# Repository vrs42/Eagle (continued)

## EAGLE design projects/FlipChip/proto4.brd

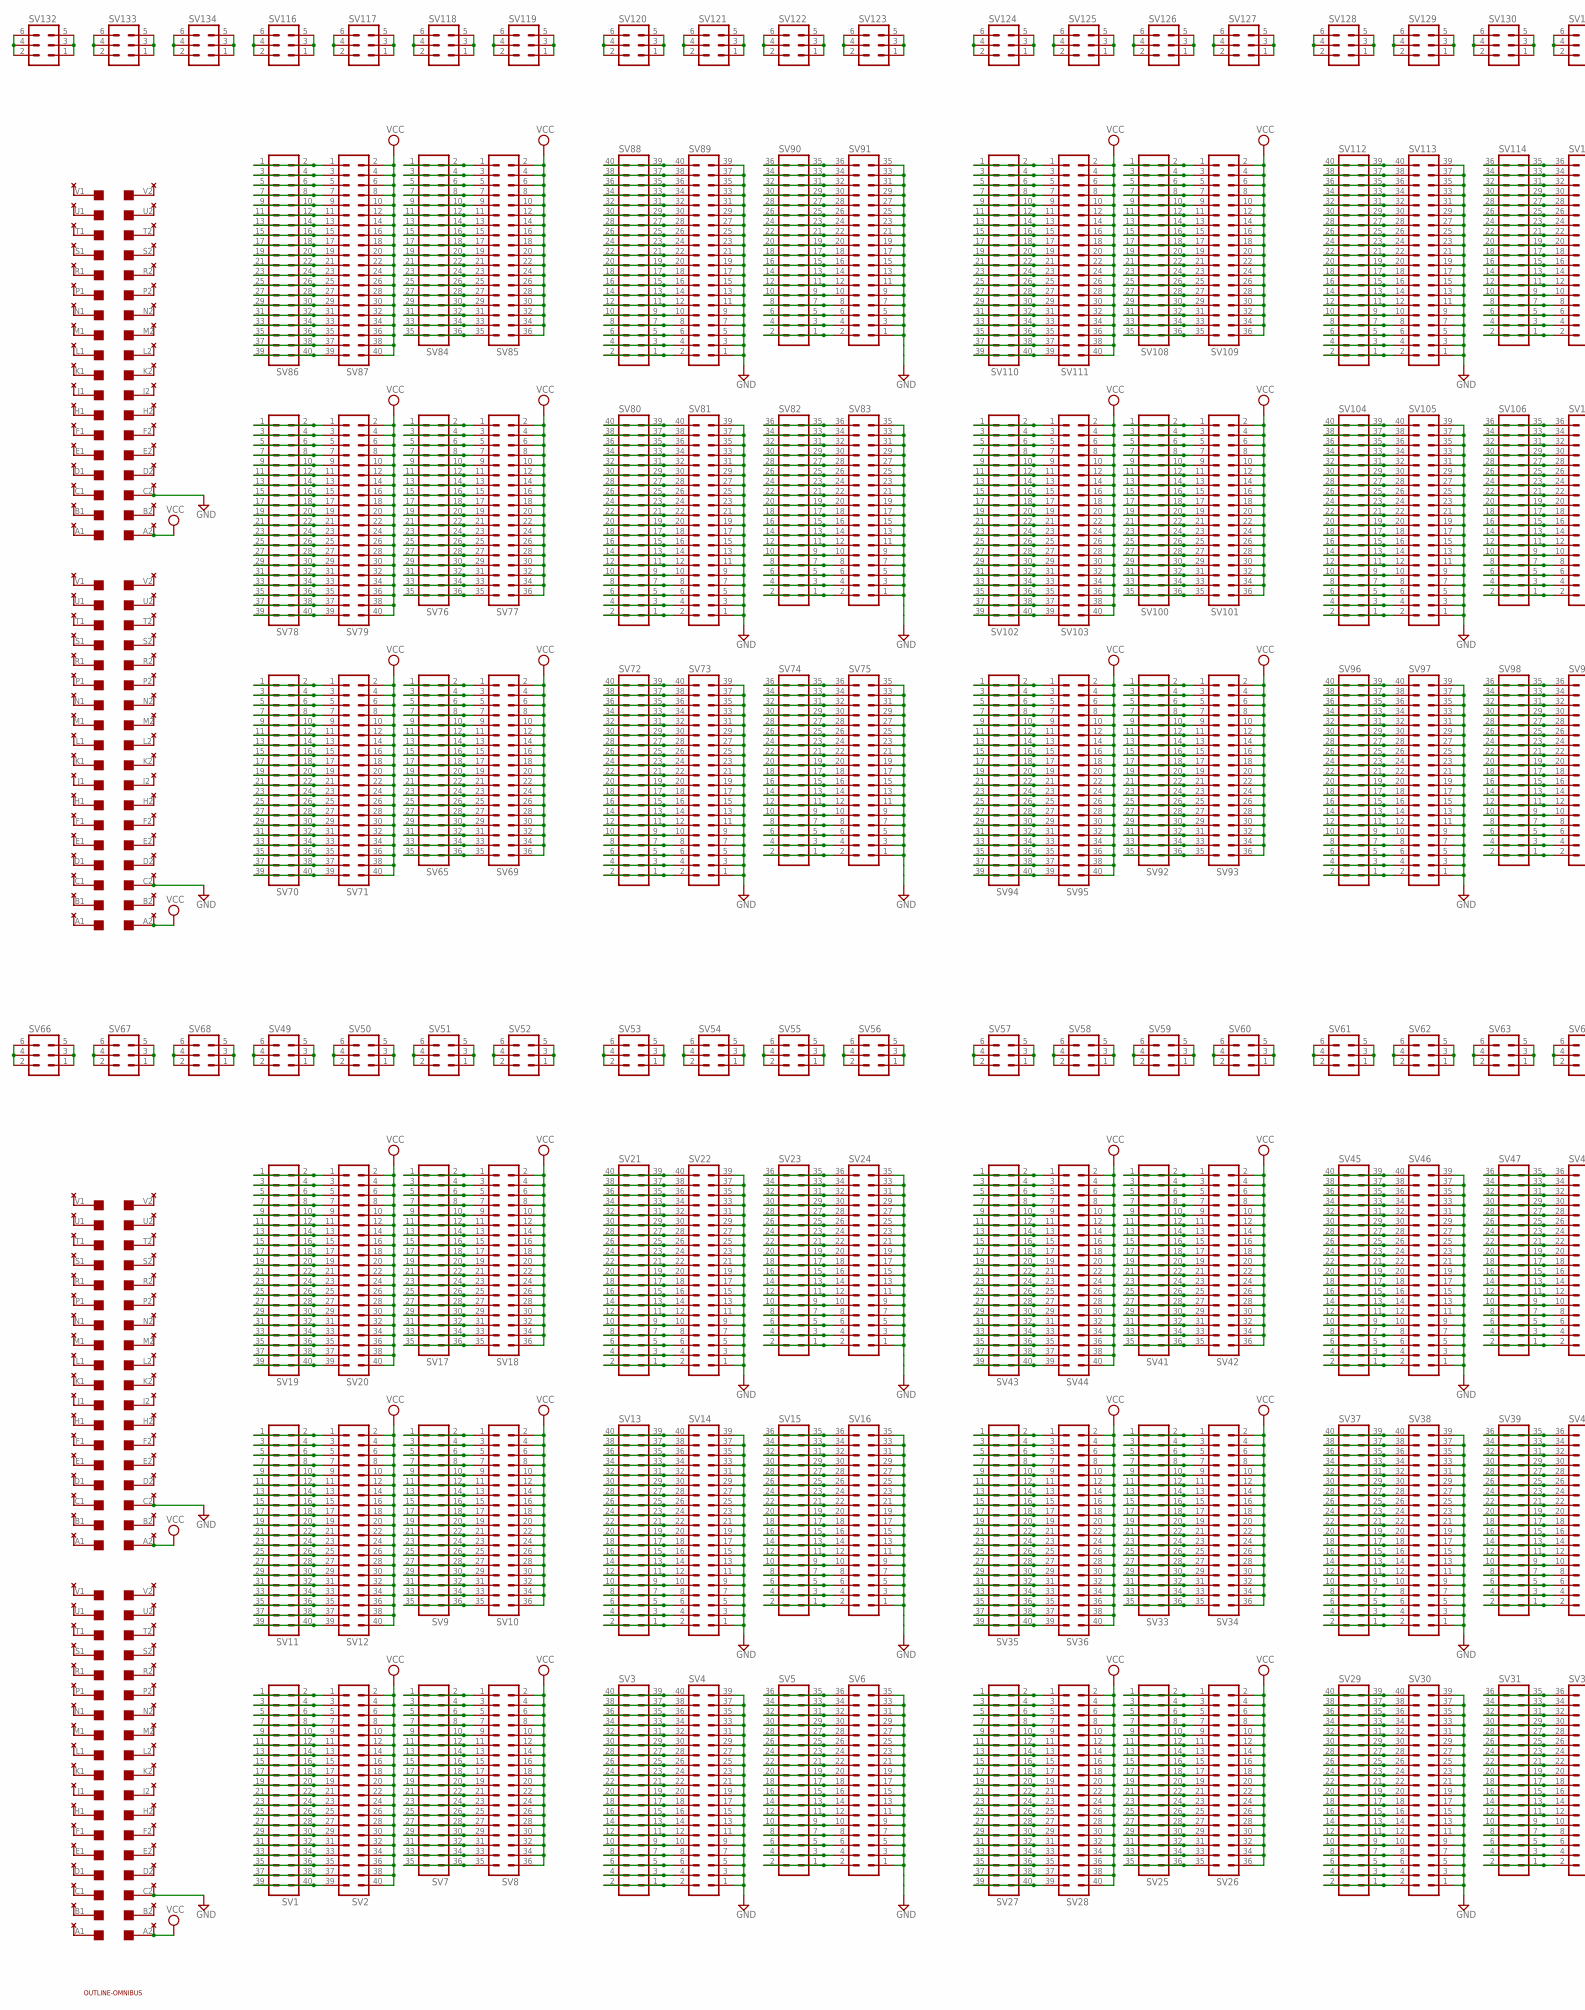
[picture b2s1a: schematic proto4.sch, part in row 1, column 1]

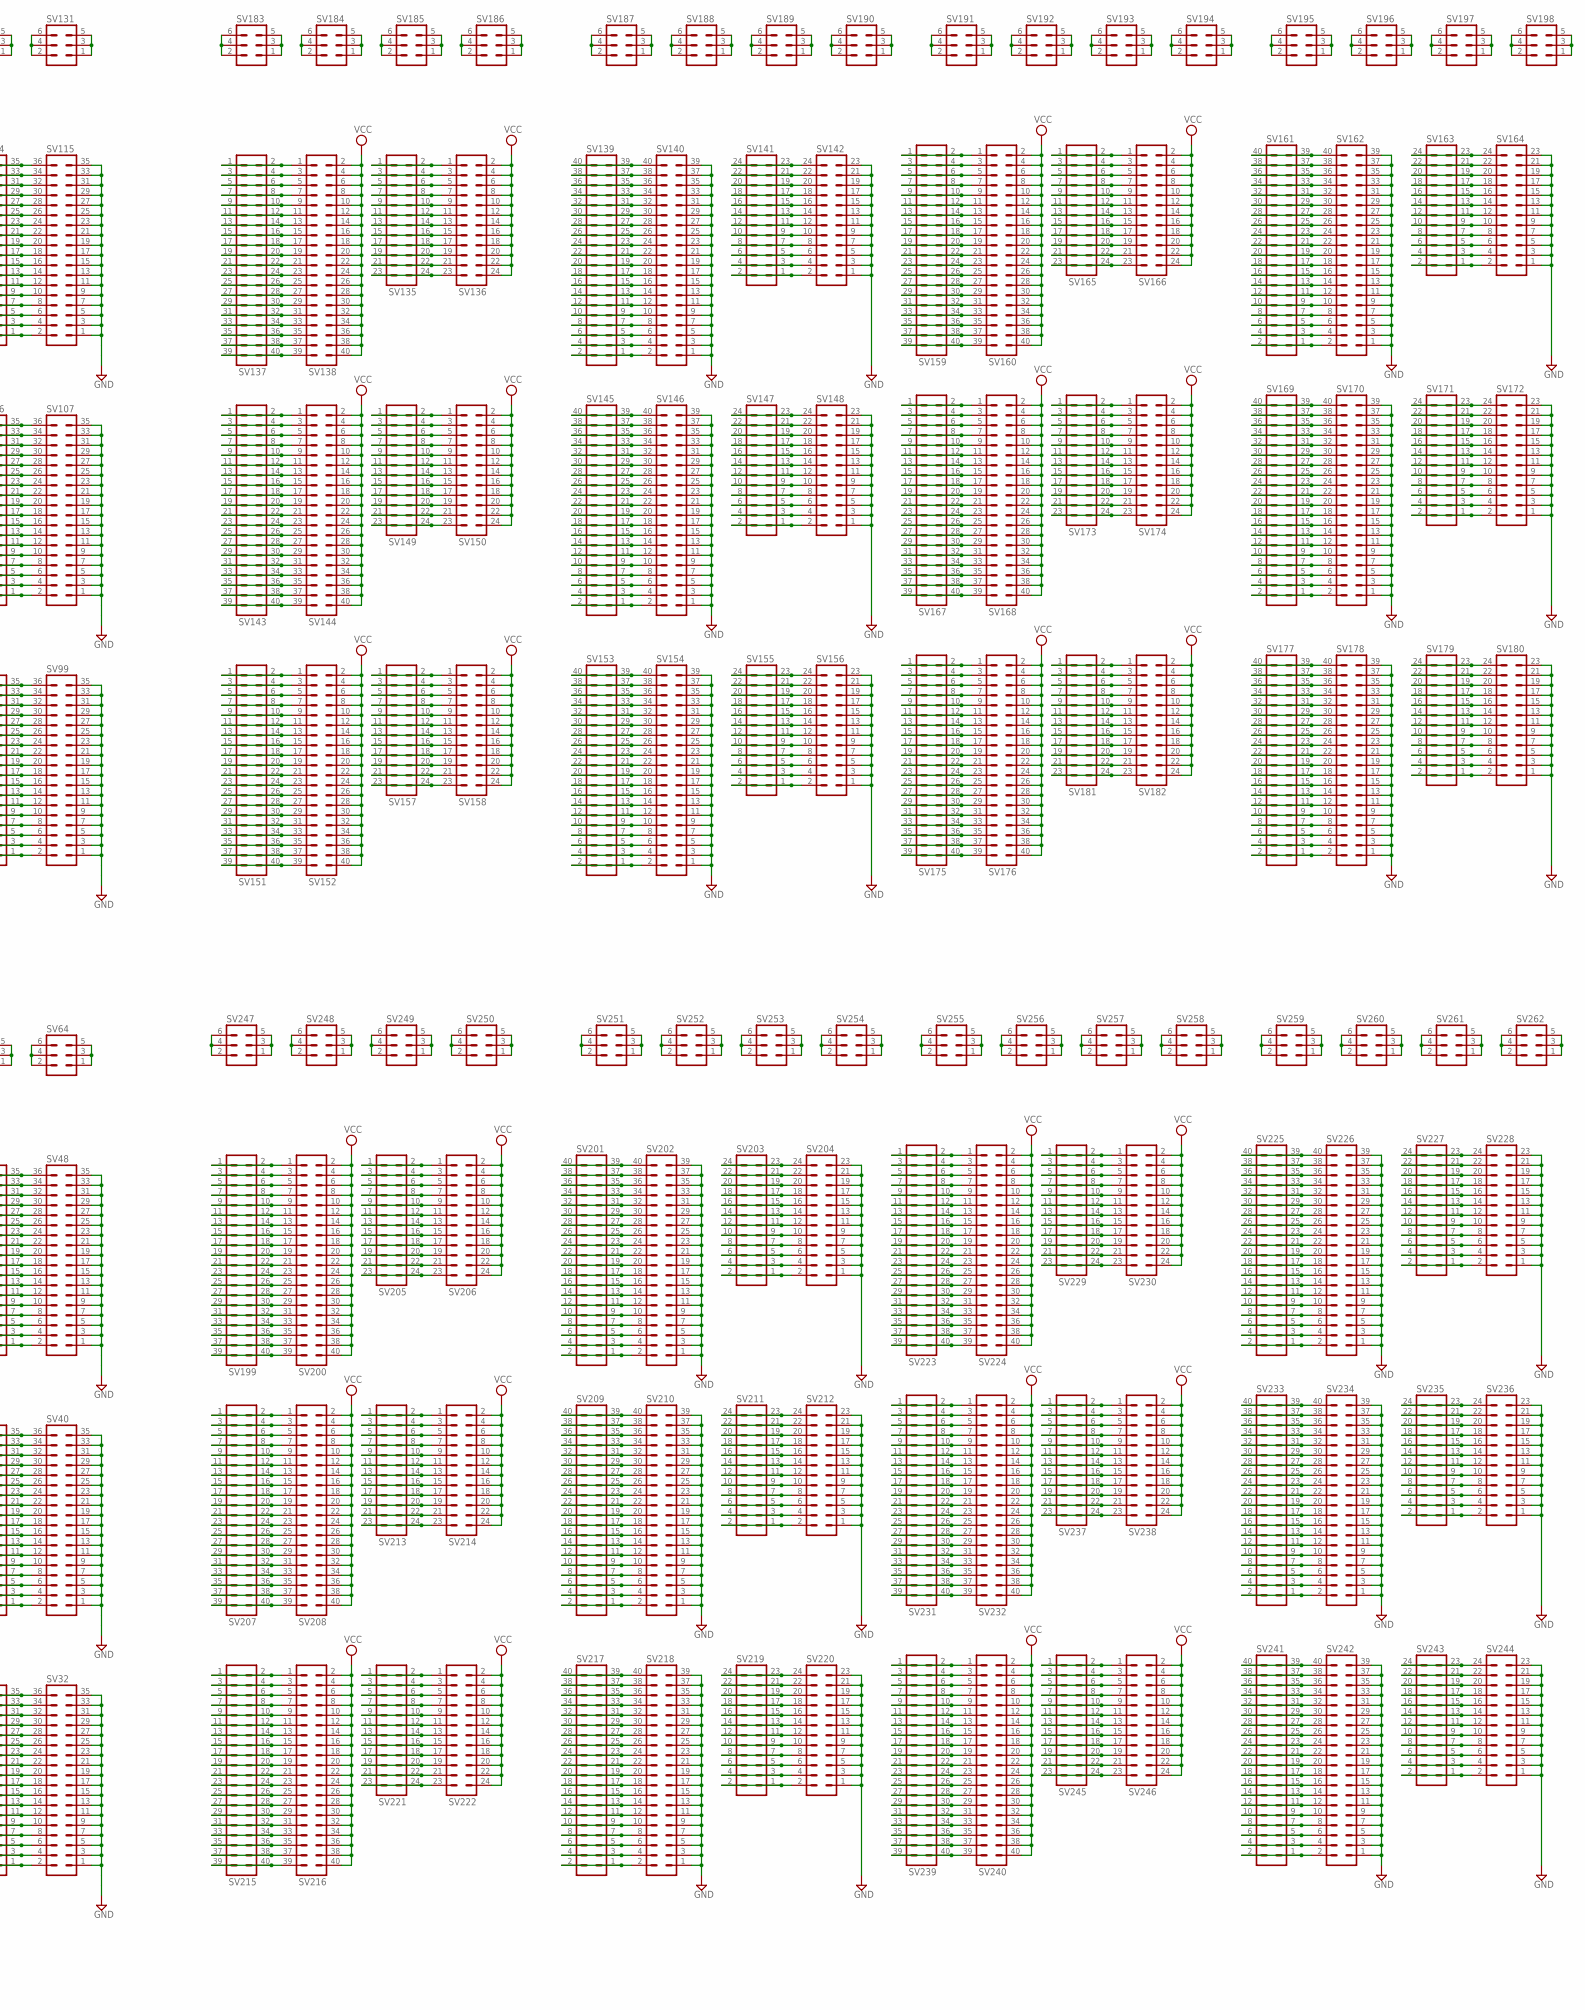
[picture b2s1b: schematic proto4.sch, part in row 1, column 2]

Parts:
A, A1: EDGE-2CONNECTOR; EDGE-CON2
B, B1: EDGE-2CONNECTOR; EDGE-CON2
SV1, SV2, SV3, SV4, SV11, SV12, SV13, SV14, SV19, SV20, SV21, SV22, SV27, SV28, SV29, SV30, SV35, SV36, SV37, SV38, SV43, SV44, SV45, SV46, SV70, SV71, SV72, SV73, SV78, SV79, SV80, SV81, SV86, SV87, SV88, SV89, SV94, SV95, SV96, SV97, SV102, SV103, SV104, SV105, SV110, SV111, SV112, SV113, SV137, SV138, SV139, SV140, SV143, SV144, SV145, SV146, SV151, SV152, SV153, SV154, SV159, SV160, SV161, SV162, SV167, SV168, SV169, SV170, SV175, SV176, SV177, SV178, SV199, SV200, SV201, SV202, SV207, SV208, SV209, SV210, SV215, SV216, SV217, SV218, SV223, SV224, SV225, SV226, SV231, SV232, SV233, SV234, SV239, SV240, SV241, SV242: MA20-2
SV5, SV6, SV7, SV8, SV9, SV10, SV15, SV16, SV17, SV18, SV23, SV24, SV25, SV26, SV31, SV32, SV33, SV34, SV39, SV40, SV41, SV42, SV47, SV48, SV65, SV69, SV74, SV75, SV76, SV77, SV82, SV83, SV84, SV85, SV90, SV91, SV92, SV93, SV98, SV99, SV100, SV101, SV106, SV107, SV108, SV109, SV114, SV115: MA18-2
SV49, SV50, SV51, SV52, SV53, SV54, SV55, SV56, SV57, SV58, SV59, SV60, SV61, SV62, SV63, SV64, SV66, SV67, SV68, SV116, SV117, SV118, SV119, SV120, SV121, SV122, SV123, SV124, SV125, SV126, SV127, SV128, SV129, SV130, SV131, SV132, SV133, SV134, SV183, SV184, SV185, SV186, SV187, SV188, SV189, SV190, SV191, SV192, SV193, SV194, SV195, SV196, SV197, SV198, SV247, SV248, SV249, SV250, SV251, SV252, SV253, SV254, SV255, SV256, SV257, SV258, SV259, SV260, SV261, SV262: MA03-2
SV135, SV136, SV141, SV142, SV147, SV148, SV149, SV150, SV155, SV156, SV157, SV158, SV163, SV164, SV165, SV166, SV171, SV172, SV173, SV174, SV179, SV180, SV181, SV182, SV203, SV204, SV205, SV206, SV211, SV212, SV213, SV214, SV219, SV220, SV221, SV222, SV227, SV228, SV229, SV230, SV235, SV236, SV237, SV238, SV243, SV244, SV245, SV246: MA12-2
U$1, U$3, U$5, U$6: THRU-HOLE2A; THRU-HOLEA
U$7: OUTLINE-OMNIBUS; OMNIBUS

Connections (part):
GND: A.C2, A1.C2, B.C2, B1.C2, SV4.1, SV4.3, SV4.5, SV4.7, SV4.9, SV4.11, SV4.13, SV4.15, SV4.17, SV4.19, SV4.21, SV4.23, SV4.25, SV4.27, SV4.29, SV4.31, SV4.33, SV4.35, SV4.37, SV4.39, SV6.1, SV6.3, SV6.5, SV6.7, SV6.9, SV6.11, SV6.13, SV6.15, SV6.17, SV6.19, SV6.21, SV6.23, SV6.25, SV6.27, SV6.29, SV6.31, SV6.33, SV6.35, SV14.1, SV14.3, SV14.5, SV14.7, SV14.9, SV14.11, SV14.13, SV14.15, SV14.17, SV14.19, SV14.21, SV14.23, SV14.25, SV14.27, SV14.29, SV14.31, SV14.33, SV14.35, SV14.37, SV14.39, SV16.1, SV16.3, SV16.5, SV16.7, SV16.9, SV16.11, SV16.13, SV16.15, SV16.17, SV16.19, SV16.21, SV16.23, SV16.25, SV16.27, SV16.29, SV16.31, SV16.33, SV16.35, SV22.1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
unnamed: A.K2, U$3.K2
unnamed: A.J2, U$3.J2
unnamed: A.H2, U$3.H2
unnamed: A.L2, U$3.L2
unnamed: A.M2, U$3.M2
unnamed: A.N2, U$3.N2
unnamed: A.P2, U$3.P2
unnamed: A.F2, U$3.F2
unnamed: A.E2, U$3.E2
unnamed: A.D2, U$3.D2
unnamed: SV1.1, SV1.2, SV2.1
unnamed: A.R2, U$3.R2
unnamed: A.S2, U$3.S2
unnamed: A.B2, U$3.B2
unnamed: SV1.3, SV1.4, SV2.3
unnamed: A.T2, U$3.T2
unnamed: A.U2, U$3.U2
unnamed: A.V2, U$3.V2
unnamed: A.A1, U$3.A1
unnamed: A.V1, U$3.V1
unnamed: A.U1, U$3.U1
unnamed: A.T1, U$3.T1
unnamed: A.S1, U$3.S1
unnamed: A.R1, U$3.R1
unnamed: A.P1, U$3.P1
unnamed: A.N1, U$3.N1
unnamed: A.M1, U$3.M1
unnamed: A.L1, U$3.L1
unnamed: A.K1, U$3.K1
unnamed: A.J1, U$3.J1
unnamed: A.H1, U$3.H1
unnamed: A.F1, U$3.F1
unnamed: A.E1, U$3.E1
unnamed: A.D1, U$3.D1
unnamed: A.C1, U$3.C1
unnamed: A.B1, U$3.B1
unnamed: SV1.5, SV1.6, SV2.5
unnamed: SV7.1, SV7.2, SV8.1
unnamed: SV7.3, SV7.4, SV8.3
unnamed: SV7.5, SV7.6, SV8.5
unnamed: SV7.7, SV7.8, SV8.7
unnamed: SV7.9, SV7.10, SV8.9
unnamed: SV7.11, SV7.12, SV8.11
unnamed: SV7.13, SV7.14, SV8.13
unnamed: SV1.7, SV1.8, SV2.7
unnamed: SV1.9, SV1.10, SV2.9
unnamed: SV1.11, SV1.12, SV2.11
unnamed: SV1.13, SV1.14, SV2.13
unnamed: SV1.15, SV1.16, SV2.15
unnamed: SV1.17, SV1.18, SV2.17
unnamed: SV1.19, SV1.20, SV2.19
unnamed: SV1.21, SV1.22, SV2.21
unnamed: SV1.23, SV1.24, SV2.23
unnamed: SV1.25, SV1.26, SV2.25
unnamed: SV1.27, SV1.28, SV2.27
unnamed: SV1.29, SV1.30, SV2.29
unnamed: SV1.31, SV1.32, SV2.31
unnamed: SV1.33, SV1.34, SV2.33
unnamed: SV1.35, SV1.36, SV2.35
unnamed: SV1.37, SV1.38, SV2.37
unnamed: SV1.39, SV1.40, SV2.39
unnamed: SV7.15, SV7.16, SV8.15
unnamed: SV7.17, SV7.18, SV8.17
unnamed: SV7.19, SV7.20, SV8.19
unnamed: SV7.21, SV7.22, SV8.21
unnamed: SV7.23, SV7.24, SV8.23
unnamed: SV7.25, SV7.26, SV8.25
unnamed: SV7.27, SV7.28, SV8.27
unnamed: SV7.29, SV7.30, SV8.29
unnamed: SV7.31, SV7.32, SV8.31
unnamed: SV7.33, SV7.34, SV8.33
unnamed: SV7.35, SV7.36, SV8.35
unnamed: SV3.39, SV3.40, SV4.40
unnamed: SV3.37, SV3.38, SV4.38
unnamed: SV3.35, SV3.36, SV4.36
unnamed: SV3.33, SV3.34, SV4.34
unnamed: SV3.31, SV3.32, SV4.32
unnamed: SV3.29, SV3.30, SV4.30
unnamed: SV3.27, SV3.28, SV4.28
unnamed: SV3.25, SV3.26, SV4.26
unnamed: SV3.23, SV3.24, SV4.24
unnamed: SV3.21, SV3.22, SV4.22
unnamed: SV3.19, SV3.20, SV4.20
unnamed: SV3.17, SV3.18, SV4.18
unnamed: SV3.15, SV3.16, SV4.16
unnamed: SV3.13, SV3.14, SV4.14
unnamed: SV3.11, SV3.12, SV4.12
unnamed: SV3.9, SV3.10, SV4.10
unnamed: SV3.7, SV3.8, SV4.8
unnamed: SV3.5, SV3.6, SV4.6
unnamed: SV3.3, SV3.4, SV4.4
unnamed: SV3.1, SV3.2, SV4.2
unnamed: SV11.1, SV11.2, SV12.1
unnamed: SV5.35, SV5.36, SV6.36
unnamed: SV5.33, SV5.34, SV6.34
unnamed: SV5.31, SV5.32, SV6.32
unnamed: SV5.29, SV5.30, SV6.30
unnamed: SV5.27, SV5.28, SV6.28
unnamed: SV5.25, SV5.26, SV6.26
unnamed: SV5.23, SV5.24, SV6.24
unnamed: SV5.21, SV5.22, SV6.22
unnamed: SV5.19, SV5.20, SV6.20
unnamed: SV5.17, SV5.18, SV6.18
unnamed: SV5.15, SV5.16, SV6.16
unnamed: SV5.13, SV5.14, SV6.14
unnamed: SV5.11, SV5.12, SV6.12
unnamed: SV5.9, SV5.10, SV6.10
unnamed: SV5.7, SV5.8, SV6.8
unnamed: SV5.5, SV5.6, SV6.6
unnamed: SV5.3, SV5.4, SV6.4
unnamed: SV5.1, SV5.2, SV6.2
unnamed: SV11.3, SV11.4, SV12.3
unnamed: SV11.5, SV11.6, SV12.5
unnamed: SV11.7, SV11.8, SV12.7
unnamed: SV11.9, SV11.10, SV12.9
unnamed: SV11.11, SV11.12, SV12.11
unnamed: SV11.13, SV11.14, SV12.13
unnamed: SV11.15, SV11.16, SV12.15
unnamed: SV11.17, SV11.18, SV12.17
unnamed: SV11.19, SV11.20, SV12.19
unnamed: SV11.21, SV11.22, SV12.21
unnamed: SV11.23, SV11.24, SV12.23
unnamed: SV11.25, SV11.26, SV12.25
unnamed: SV11.27, SV11.28, SV12.27
unnamed: SV11.29, SV11.30, SV12.29
unnamed: SV11.31, SV11.32, SV12.31
unnamed: SV11.33, SV11.34, SV12.33
unnamed: SV11.35, SV11.36, SV12.35
unnamed: SV11.37, SV11.38, SV12.37
unnamed: SV11.39, SV11.40, SV12.39
unnamed: SV9.1, SV9.2, SV10.1
unnamed: SV9.3, SV9.4, SV10.3
unnamed: SV9.5, SV9.6, SV10.5
unnamed: SV9.7, SV9.8, SV10.7
unnamed: SV9.9, SV9.10, SV10.9
unnamed: SV9.11, SV9.12, SV10.11
unnamed: SV9.13, SV9.14, SV10.13
unnamed: SV9.15, SV9.16, SV10.15
unnamed: SV9.17, SV9.18, SV10.17
unnamed: SV9.19, SV9.20, SV10.19
unnamed: SV9.21, SV9.22, SV10.21
unnamed: SV9.23, SV9.24, SV10.23
unnamed: SV9.25, SV9.26, SV10.25
unnamed: SV9.27, SV9.28, SV10.27
unnamed: SV9.29, SV9.30, SV10.29
unnamed: SV9.31, SV9.32, SV10.31
unnamed: SV9.33, SV9.34, SV10.33
unnamed: SV9.35, SV9.36, SV10.35
unnamed: SV13.39, SV13.40, SV14.40
unnamed: SV13.37, SV13.38, SV14.38
unnamed: SV13.35, SV13.36, SV14.36
unnamed: SV13.33, SV13.34, SV14.34
unnamed: SV13.31, SV13.32, SV14.32
unnamed: SV13.29, SV13.30, SV14.30
unnamed: SV13.27, SV13.28, SV14.28
unnamed: SV13.25, SV13.26, SV14.26
unnamed: SV13.23, SV13.24, SV14.24
unnamed: SV13.21, SV13.22, SV14.22
unnamed: SV13.19, SV13.20, SV14.20
unnamed: SV13.17, SV13.18, SV14.18
unnamed: SV13.15, SV13.16, SV14.16
unnamed: SV13.13, SV13.14, SV14.14
unnamed: SV13.11, SV13.12, SV14.12
unnamed: SV13.9, SV13.10, SV14.10
unnamed: SV13.7, SV13.8, SV14.8
unnamed: SV13.5, SV13.6, SV14.6
unnamed: SV13.3, SV13.4, SV14.4
unnamed: SV13.1, SV13.2, SV14.2
unnamed: SV15.35, SV15.36, SV16.36
unnamed: SV15.33, SV15.34, SV16.34
unnamed: SV15.31, SV15.32, SV16.32
unnamed: SV15.29, SV15.30, SV16.30
unnamed: SV15.27, SV15.28, SV16.28
unnamed: SV15.25, SV15.26, SV16.26
unnamed: SV15.23, SV15.24, SV16.24
unnamed: SV15.21, SV15.22, SV16.22
unnamed: SV15.19, SV15.20, SV16.20
unnamed: SV15.17, SV15.18, SV16.18
unnamed: SV15.15, SV15.16, SV16.16
unnamed: SV15.13, SV15.14, SV16.14
unnamed: SV15.11, SV15.12, SV16.12
unnamed: SV15.9, SV15.10, SV16.10
unnamed: SV15.7, SV15.8, SV16.8
unnamed: SV15.5, SV15.6, SV16.6
unnamed: SV15.3, SV15.4, SV16.4
unnamed: SV15.1, SV15.2, SV16.2
unnamed: SV19.1, SV19.2, SV20.1
unnamed: SV19.3, SV19.4, SV20.3
unnamed: SV19.5, SV19.6, SV20.5
unnamed: SV19.7, SV19.8, SV20.7
unnamed: SV19.9, SV19.10, SV20.9
unnamed: SV19.11, SV19.12, SV20.11
unnamed: SV19.13, SV19.14, SV20.13
unnamed: SV19.15, SV19.16, SV20.15
unnamed: SV19.17, SV19.18, SV20.17
unnamed: SV19.19, SV19.20, SV20.19
unnamed: SV19.21, SV19.22, SV20.21
unnamed: SV19.23, SV19.24, SV20.23
unnamed: SV19.25, SV19.26, SV20.25
unnamed: SV19.27, SV19.28, SV20.27
unnamed: SV19.29, SV19.30, SV20.29
unnamed: SV19.31, SV19.32, SV20.31
unnamed: SV19.33, SV19.34, SV20.33
unnamed: SV19.35, SV19.36, SV20.35
unnamed: SV19.37, SV19.38, SV20.37
unnamed: SV19.39, SV19.40, SV20.39
unnamed: SV17.1, SV17.2, SV18.1
unnamed: SV17.3, SV17.4, SV18.3
unnamed: SV17.5, SV17.6, SV18.5
unnamed: SV17.7, SV17.8, SV18.7
unnamed: SV17.9, SV17.10, SV18.9
unnamed: SV17.11, SV17.12, SV18.11
unnamed: SV17.13, SV17.14, SV18.13
unnamed: SV17.15, SV17.16, SV18.15
unnamed: SV17.17, SV17.18, SV18.17
unnamed: SV17.19, SV17.20, SV18.19
unnamed: SV17.21, SV17.22, SV18.21
unnamed: SV17.23, SV17.24, SV18.23
unnamed: SV17.25, SV17.26, SV18.25
unnamed: SV17.27, SV17.28, SV18.27
unnamed: SV17.29, SV17.30, SV18.29
unnamed: SV17.31, SV17.32, SV18.31
unnamed: SV17.33, SV17.34, SV18.33
unnamed: SV17.35, SV17.36, SV18.35
unnamed: SV21.39, SV21.40, SV22.40
unnamed: SV21.37, SV21.38, SV22.38
unnamed: SV21.35, SV21.36, SV22.36
unnamed: SV21.33, SV21.34, SV22.34
unnamed: SV21.31, SV21.32, SV22.32
unnamed: SV21.29, SV21.30, SV22.30
unnamed: SV21.27, SV21.28, SV22.28
unnamed: SV21.25, SV21.26, SV22.26
unnamed: SV21.23, SV21.24, SV22.24
unnamed: SV21.21, SV21.22, SV22.22
unnamed: SV21.19, SV21.20, SV22.20
unnamed: SV21.17, SV21.18, SV22.18
unnamed: SV21.15, SV21.16, SV22.16
unnamed: SV21.13, SV21.14, SV22.14
unnamed: SV21.11, SV21.12, SV22.12
unnamed: SV21.9, SV21.10, SV22.10
unnamed: SV21.7, SV21.8, SV22.8
unnamed: SV21.5, SV21.6, SV22.6
unnamed: SV21.3, SV21.4, SV22.4
unnamed: SV21.1, SV21.2, SV22.2
unnamed: SV23.35, SV23.36, SV24.36
unnamed: SV23.33, SV23.34, SV24.34
unnamed: SV23.31, SV23.32, SV24.32
unnamed: SV23.29, SV23.30, SV24.30
unnamed: SV23.27, SV23.28, SV24.28
unnamed: SV23.25, SV23.26, SV24.26
unnamed: SV23.23, SV23.24, SV24.24
unnamed: SV23.21, SV23.22, SV24.22
unnamed: SV23.19, SV23.20, SV24.20
unnamed: SV23.17, SV23.18, SV24.18
unnamed: SV23.15, SV23.16, SV24.16
unnamed: SV23.13, SV23.14, SV24.14
unnamed: SV23.11, SV23.12, SV24.12
unnamed: SV23.9, SV23.10, SV24.10
unnamed: SV23.7, SV23.8, SV24.8
unnamed: SV23.5, SV23.6, SV24.6
unnamed: SV23.3, SV23.4, SV24.4
unnamed: SV23.1, SV23.2, SV24.2
unnamed: B.K2, U$5.K2
unnamed: B.J2, U$5.J2
unnamed: B.H2, U$5.H2
unnamed: B.L2, U$5.L2
unnamed: B.M2, U$5.M2
unnamed: B.N2, U$5.N2
unnamed: B.P2, U$5.P2
unnamed: B.F2, U$5.F2
unnamed: B.E2, U$5.E2
unnamed: B.D2, U$5.D2
unnamed: B.R2, U$5.R2
unnamed: B.S2, U$5.S2
unnamed: B.B2, U$5.B2
unnamed: B.T2, U$5.T2
unnamed: B.U2, U$5.U2
unnamed: B.V2, U$5.V2
unnamed: B.A1, U$5.A1
unnamed: B.V1, U$5.V1
unnamed: B.U1, U$5.U1
unnamed: B.T1, U$5.T1
unnamed: B.S1, U$5.S1
unnamed: B.R1, U$5.R1
unnamed: B.P1, U$5.P1
unnamed: B.N1, U$5.N1
unnamed: B.M1, U$5.M1
unnamed: B.L1, U$5.L1
unnamed: B.K1, U$5.K1
unnamed: B.J1, U$5.J1
unnamed: B.H1, U$5.H1
unnamed: B.F1, U$5.F1
unnamed: B.E1, U$5.E1
unnamed: B.D1, U$5.D1
unnamed: B.C1, U$5.C1
unnamed: B.B1, U$5.B1
unnamed: SV27.1, SV27.2, SV28.1
unnamed: SV27.3, SV27.4, SV28.3
unnamed: SV27.5, SV27.6, SV28.5
unnamed: SV27.7, SV27.8, SV28.7
unnamed: SV27.9, SV27.10, SV28.9
unnamed: SV27.11, SV27.12, SV28.11
unnamed: SV27.13, SV27.14, SV28.13
unnamed: SV27.15, SV27.16, SV28.15
unnamed: SV27.17, SV27.18, SV28.17
unnamed: SV27.19, SV27.20, SV28.19
unnamed: SV27.21, SV27.22, SV28.21
unnamed: SV27.23, SV27.24, SV28.23
unnamed: SV27.25, SV27.26, SV28.25
unnamed: SV27.27, SV27.28, SV28.27
unnamed: SV27.29, SV27.30, SV28.29
unnamed: SV27.31, SV27.32, SV28.31
unnamed: SV27.33, SV27.34, SV28.33
unnamed: SV27.35, SV27.36, SV28.35
unnamed: SV27.37, SV27.38, SV28.37
unnamed: SV27.39, SV27.40, SV28.39
unnamed: SV25.1, SV25.2, SV26.1
unnamed: SV25.3, SV25.4, SV26.3
unnamed: SV25.5, SV25.6, SV26.5
unnamed: SV25.7, SV25.8, SV26.7
unnamed: SV25.9, SV25.10, SV26.9
unnamed: SV25.11, SV25.12, SV26.11
unnamed: SV25.13, SV25.14, SV26.13
unnamed: SV25.15, SV25.16, SV26.15
unnamed: SV25.17, SV25.18, SV26.17
unnamed: SV25.19, SV25.20, SV26.19
unnamed: SV25.21, SV25.22, SV26.21
unnamed: SV25.23, SV25.24, SV26.23
unnamed: SV25.25, SV25.26, SV26.25
unnamed: SV25.27, SV25.28, SV26.27
unnamed: SV25.29, SV25.30, SV26.29
unnamed: SV25.31, SV25.32, SV26.31
unnamed: SV25.33, SV25.34, SV26.33
unnamed: SV25.35, SV25.36, SV26.35
unnamed: SV29.39, SV29.40, SV30.40
unnamed: SV29.37, SV29.38, SV30.38
unnamed: SV29.35, SV29.36, SV30.36
unnamed: SV29.33, SV29.34, SV30.34
unnamed: SV29.31, SV29.32, SV30.32
unnamed: SV29.29, SV29.30, SV30.30
unnamed: SV29.27, SV29.28, SV30.28
unnamed: SV29.25, SV29.26, SV30.26
unnamed: SV29.23, SV29.24, SV30.24
unnamed: SV29.21, SV29.22, SV30.22
unnamed: SV29.19, SV29.20, SV30.20
unnamed: SV29.17, SV29.18, SV30.18
unnamed: SV29.15, SV29.16, SV30.16
unnamed: SV29.13, SV29.14, SV30.14
unnamed: SV29.11, SV29.12, SV30.12
unnamed: SV29.9, SV29.10, SV30.10
unnamed: SV29.7, SV29.8, SV30.8
unnamed: SV29.5, SV29.6, SV30.6
unnamed: SV29.3, SV29.4, SV30.4
unnamed: SV29.1, SV29.2, SV30.2
unnamed: SV31.35, SV31.36, SV32.36
unnamed: SV31.33, SV31.34, SV32.34
unnamed: SV31.31, SV31.32, SV32.32
unnamed: SV31.29, SV31.30, SV32.30
unnamed: SV31.27, SV31.28, SV32.28
unnamed: SV31.25, SV31.26, SV32.26
unnamed: SV31.23, SV31.24, SV32.24
unnamed: SV31.21, SV31.22, SV32.22
unnamed: SV31.19, SV31.20, SV32.20
unnamed: SV31.17, SV31.18, SV32.18
unnamed: SV31.15, SV31.16, SV32.16
unnamed: SV31.13, SV31.14, SV32.14
unnamed: SV31.11, SV31.12, SV32.12
unnamed: SV31.9, SV31.10, SV32.10
unnamed: SV31.7, SV31.8, SV32.8
unnamed: SV31.5, SV31.6, SV32.6
unnamed: SV31.3, SV31.4, SV32.4
unnamed: SV31.1, SV31.2, SV32.2
unnamed: SV35.1, SV35.2, SV36.1
unnamed: SV35.3, SV35.4, SV36.3
unnamed: SV35.5, SV35.6, SV36.5
unnamed: SV35.7, SV35.8, SV36.7
unnamed: SV35.9, SV35.10, SV36.9
unnamed: SV35.11, SV35.12, SV36.11
unnamed: SV35.13, SV35.14, SV36.13
unnamed: SV35.15, SV35.16, SV36.15
unnamed: SV35.17, SV35.18, SV36.17
unnamed: SV35.19, SV35.20, SV36.19
unnamed: SV35.21, SV35.22, SV36.21
unnamed: SV35.23, SV35.24, SV36.23
unnamed: SV35.25, SV35.26, SV36.25
unnamed: SV35.27, SV35.28, SV36.27
unnamed: SV35.29, SV35.30, SV36.29
unnamed: SV35.31, SV35.32, SV36.31
unnamed: SV35.33, SV35.34, SV36.33
unnamed: SV35.35, SV35.36, SV36.35
unnamed: SV35.37, SV35.38, SV36.37
unnamed: SV35.39, SV35.40, SV36.39
unnamed: SV33.1, SV33.2, SV34.1
unnamed: SV33.3, SV33.4, SV34.3
unnamed: SV33.5, SV33.6, SV34.5
unnamed: SV33.7, SV33.8, SV34.7
unnamed: SV33.9, SV33.10, SV34.9
unnamed: SV33.11, SV33.12, SV34.11
unnamed: SV33.13, SV33.14, SV34.13
unnamed: SV33.15, SV33.16, SV34.15
unnamed: SV33.17, SV33.18, SV34.17
unnamed: SV33.19, SV33.20, SV34.19
unnamed: SV33.21, SV33.22, SV34.21
unnamed: SV33.23, SV33.24, SV34.23
unnamed: SV33.25, SV33.26, SV34.25
unnamed: SV33.27, SV33.28, SV34.27
unnamed: SV33.29, SV33.30, SV34.29
unnamed: SV33.31, SV33.32, SV34.31
unnamed: SV33.33, SV33.34, SV34.33
unnamed: SV33.35, SV33.36, SV34.35
unnamed: SV37.39, SV37.40, SV38.40
unnamed: SV37.37, SV37.38, SV38.38
unnamed: SV37.35, SV37.36, SV38.36
unnamed: SV37.33, SV37.34, SV38.34
unnamed: SV37.31, SV37.32, SV38.32
unnamed: SV37.29, SV37.30, SV38.30
unnamed: SV37.27, SV37.28, SV38.28
unnamed: SV37.25, SV37.26, SV38.26
unnamed: SV37.23, SV37.24, SV38.24
unnamed: SV37.21, SV37.22, SV38.22
unnamed: SV37.19, SV37.20, SV38.20
unnamed: SV37.17, SV37.18, SV38.18
unnamed: SV37.15, SV37.16, SV38.16
unnamed: SV37.13, SV37.14, SV38.14
unnamed: SV37.11, SV37.12, SV38.12
unnamed: SV37.9, SV37.10, SV38.10
unnamed: SV37.7, SV37.8, SV38.8
unnamed: SV37.5, SV37.6, SV38.6
unnamed: SV37.3, SV37.4, SV38.4
unnamed: SV37.1, SV37.2, SV38.2
unnamed: SV39.35, SV39.36, SV40.36
unnamed: SV39.33, SV39.34, SV40.34
unnamed: SV39.31, SV39.32, SV40.32
unnamed: SV39.29, SV39.30, SV40.30
unnamed: SV39.27, SV39.28, SV40.28
unnamed: SV39.25, SV39.26, SV40.26
unnamed: SV39.23, SV39.24, SV40.24
unnamed: SV39.21, SV39.22, SV40.22
unnamed: SV39.19, SV39.20, SV40.20
unnamed: SV39.17, SV39.18, SV40.18
unnamed: SV39.15, SV39.16, SV40.16
unnamed: SV39.13, SV39.14, SV40.14
unnamed: SV39.11, SV39.12, SV40.12
unnamed: SV39.9, SV39.10, SV40.10
unnamed: SV39.7, SV39.8, SV40.8
unnamed: SV39.5, SV39.6, SV40.6
unnamed: SV39.3, SV39.4, SV40.4
unnamed: SV39.1, SV39.2, SV40.2
unnamed: SV43.1, SV43.2, SV44.1
unnamed: SV43.3, SV43.4, SV44.3
unnamed: SV43.5, SV43.6, SV44.5
unnamed: SV43.7, SV43.8, SV44.7
unnamed: SV43.9, SV43.10, SV44.9
unnamed: SV43.11, SV43.12, SV44.11
unnamed: SV43.13, SV43.14, SV44.13
unnamed: SV43.15, SV43.16, SV44.15
unnamed: SV43.17, SV43.18, SV44.17
unnamed: SV43.19, SV43.20, SV44.19
unnamed: SV43.21, SV43.22, SV44.21
unnamed: SV43.23, SV43.24, SV44.23
unnamed: SV43.25, SV43.26, SV44.25
unnamed: SV43.27, SV43.28, SV44.27
unnamed: SV43.29, SV43.30, SV44.29
unnamed: SV43.31, SV43.32, SV44.31
unnamed: SV43.33, SV43.34, SV44.33
unnamed: SV43.35, SV43.36, SV44.35
unnamed: SV43.37, SV43.38, SV44.37
unnamed: SV43.39, SV43.40, SV44.39
unnamed: SV41.1, SV41.2, SV42.1
unnamed: SV41.3, SV41.4, SV42.3
unnamed: SV41.5, SV41.6, SV42.5
unnamed: SV41.7, SV41.8, SV42.7
unnamed: SV41.9, SV41.10, SV42.9
unnamed: SV41.11, SV41.12, SV42.11
unnamed: SV41.13, SV41.14, SV42.13
unnamed: SV41.15, SV41.16, SV42.15
unnamed: SV41.17, SV41.18, SV42.17
unnamed: SV41.19, SV41.20, SV42.19
unnamed: SV41.21, SV41.22, SV42.21
unnamed: SV41.23, SV41.24, SV42.23
unnamed: SV41.25, SV41.26, SV42.25
unnamed: SV41.27, SV41.28, SV42.27
unnamed: SV41.29, SV41.30, SV42.29
unnamed: SV41.31, SV41.32, SV42.31
unnamed: SV41.33, SV41.34, SV42.33
unnamed: SV41.35, SV41.36, SV42.35
unnamed: SV45.39, SV45.40, SV46.40
unnamed: SV45.37, SV45.38, SV46.38
unnamed: SV45.35, SV45.36, SV46.36
unnamed: SV45.33, SV45.34, SV46.34
unnamed: SV45.31, SV45.32, SV46.32
unnamed: SV45.29, SV45.30, SV46.30
unnamed: SV45.27, SV45.28, SV46.28
unnamed: SV45.25, SV45.26, SV46.26
unnamed: SV45.23, SV45.24, SV46.24
unnamed: SV45.21, SV45.22, SV46.22
unnamed: SV45.19, SV45.20, SV46.20
unnamed: SV45.17, SV45.18, SV46.18
unnamed: SV45.15, SV45.16, SV46.16
unnamed: SV45.13, SV45.14, SV46.14
unnamed: SV45.11, SV45.12, SV46.12
unnamed: SV45.9, SV45.10, SV46.10
unnamed: SV45.7, SV45.8, SV46.8
unnamed: SV45.5, SV45.6, SV46.6
unnamed: SV45.3, SV45.4, SV46.4
unnamed: SV45.1, SV45.2, SV46.2
unnamed: SV47.35, SV47.36, SV48.36
unnamed: SV47.33, SV47.34, SV48.34
unnamed: SV47.31, SV47.32, SV48.32
unnamed: SV47.29, SV47.30, SV48.30
unnamed: SV47.27, SV47.28, SV48.28
unnamed: SV47.25, SV47.26, SV48.26
unnamed: SV47.23, SV47.24, SV48.24
unnamed: SV47.21, SV47.22, SV48.22
unnamed: SV47.19, SV47.20, SV48.20
unnamed: SV47.17, SV47.18, SV48.18
unnamed: SV47.15, SV47.16, SV48.16
unnamed: SV47.13, SV47.14, SV48.14
unnamed: SV47.11, SV47.12, SV48.12
unnamed: SV47.9, SV47.10, SV48.10
unnamed: SV47.7, SV47.8, SV48.8
unnamed: SV47.5, SV47.6, SV48.6
unnamed: SV47.3, SV47.4, SV48.4
unnamed: SV47.1, SV47.2, SV48.2
unnamed: SV66.2, SV66.4, SV66.6
unnamed: SV66.1, SV66.3, SV66.5
unnamed: SV67.2, SV67.4, SV67.6
unnamed: SV67.1, SV67.3, SV67.5
unnamed: SV68.2, SV68.4, SV68.6
unnamed: SV68.1, SV68.3, SV68.5
unnamed: SV49.2, SV49.4, SV49.6
unnamed: SV49.1, SV49.3, SV49.5
unnamed: SV50.2, SV50.4, SV50.6
unnamed: SV50.1, SV50.3, SV50.5
unnamed: SV51.2, SV51.4, SV51.6
unnamed: SV51.1, SV51.3, SV51.5
unnamed: SV52.1, SV52.3, SV52.5
unnamed: SV52.2, SV52.4, SV52.6
unnamed: SV53.2, SV53.4, SV53.6
unnamed: SV53.1, SV53.3, SV53.5
unnamed: SV54.2, SV54.4, SV54.6
unnamed: SV54.1, SV54.3, SV54.5
unnamed: SV55.2, SV55.4, SV55.6
unnamed: SV55.1, SV55.3, SV55.5
unnamed: SV56.2, SV56.4, SV56.6
unnamed: SV56.1, SV56.3, SV56.5
unnamed: SV57.2, SV57.4, SV57.6
unnamed: SV57.1, SV57.3, SV57.5
unnamed: SV58.2, SV58.4, SV58.6
unnamed: SV58.1, SV58.3, SV58.5
unnamed: SV59.2, SV59.4, SV59.6
unnamed: SV59.1, SV59.3, SV59.5
unnamed: SV60.2, SV60.4, SV60.6
unnamed: SV60.1, SV60.3, SV60.5
unnamed: SV61.2, SV61.4, SV61.6
unnamed: SV61.1, SV61.3, SV61.5
unnamed: SV62.2, SV62.4, SV62.6
unnamed: SV62.1, SV62.3, SV62.5
unnamed: SV63.2, SV63.4, SV63.6
unnamed: SV63.1, SV63.3, SV63.5
unnamed: SV64.2, SV64.4, SV64.6
unnamed: SV64.1, SV64.3, SV64.5
unnamed: A1.K2, U$1.K2
unnamed: A1.J2, U$1.J2
unnamed: A1.H2, U$1.H2
unnamed: A1.L2, U$1.L2
unnamed: A1.M2, U$1.M2
unnamed: A1.N2, U$1.N2
unnamed: A1.P2, U$1.P2
unnamed: A1.F2, U$1.F2
unnamed: A1.E2, U$1.E2
unnamed: A1.D2, U$1.D2
unnamed: A1.R2, U$1.R2
unnamed: A1.S2, U$1.S2
unnamed: A1.B2, U$1.B2
unnamed: A1.T2, U$1.T2
unnamed: A1.U2, U$1.U2
unnamed: A1.V2, U$1.V2
unnamed: A1.A1, U$1.A1
unnamed: A1.V1, U$1.V1
unnamed: A1.U1, U$1.U1
unnamed: A1.T1, U$1.T1
unnamed: A1.S1, U$1.S1
unnamed: A1.R1, U$1.R1
unnamed: A1.P1, U$1.P1
unnamed: A1.N1, U$1.N1
unnamed: A1.M1, U$1.M1
unnamed: A1.L1, U$1.L1
unnamed: A1.K1, U$1.K1
unnamed: A1.J1, U$1.J1
unnamed: A1.H1, U$1.H1
unnamed: A1.F1, U$1.F1
unnamed: A1.E1, U$1.E1
unnamed: A1.D1, U$1.D1
unnamed: A1.C1, U$1.C1
unnamed: A1.B1, U$1.B1
unnamed: SV70.1, SV70.2, SV71.1
unnamed: SV70.3, SV70.4, SV71.3
unnamed: SV70.5, SV70.6, SV71.5
unnamed: SV70.7, SV70.8, SV71.7
unnamed: SV70.9, SV70.10, SV71.9
unnamed: SV70.11, SV70.12, SV71.11
unnamed: SV70.13, SV70.14, SV71.13
unnamed: SV70.15, SV70.16, SV71.15
unnamed: SV70.17, SV70.18, SV71.17
unnamed: SV70.19, SV70.20, SV71.19
unnamed: SV70.21, SV70.22, SV71.21
unnamed: SV70.23, SV70.24, SV71.23
unnamed: SV70.25, SV70.26, SV71.25
unnamed: SV70.27, SV70.28, SV71.27
unnamed: SV70.29, SV70.30, SV71.29
unnamed: SV70.31, SV70.32, SV71.31
unnamed: SV70.33, SV70.34, SV71.33
unnamed: SV70.35, SV70.36, SV71.35
unnamed: SV70.37, SV70.38, SV71.37
unnamed: SV70.39, SV70.40, SV71.39
unnamed: SV65.1, SV65.2, SV69.1
unnamed: SV65.3, SV65.4, SV69.3
unnamed: SV65.5, SV65.6, SV69.5
unnamed: SV65.7, SV65.8, SV69.7
unnamed: SV65.9, SV65.10, SV69.9
unnamed: SV65.11, SV65.12, SV69.11
unnamed: SV65.13, SV65.14, SV69.13
unnamed: SV65.15, SV65.16, SV69.15
unnamed: SV65.17, SV65.18, SV69.17
unnamed: SV65.19, SV65.20, SV69.19
unnamed: SV65.21, SV65.22, SV69.21
unnamed: SV65.23, SV65.24, SV69.23
unnamed: SV65.25, SV65.26, SV69.25
unnamed: SV65.27, SV65.28, SV69.27
unnamed: SV65.29, SV65.30, SV69.29
unnamed: SV65.31, SV65.32, SV69.31
unnamed: SV65.33, SV65.34, SV69.33
unnamed: SV65.35, SV65.36, SV69.35
unnamed: SV72.39, SV72.40, SV73.40
unnamed: SV72.37, SV72.38, SV73.38
unnamed: SV72.35, SV72.36, SV73.36
unnamed: SV72.33, SV72.34, SV73.34
unnamed: SV72.31, SV72.32, SV73.32
unnamed: SV72.29, SV72.30, SV73.30
unnamed: SV72.27, SV72.28, SV73.28
unnamed: SV72.25, SV72.26, SV73.26
unnamed: SV72.23, SV72.24, SV73.24
unnamed: SV72.21, SV72.22, SV73.22
unnamed: SV72.19, SV72.20, SV73.20
unnamed: SV72.17, SV72.18, SV73.18
unnamed: SV72.15, SV72.16, SV73.16
unnamed: SV72.13, SV72.14, SV73.14
unnamed: SV72.11, SV72.12, SV73.12
unnamed: SV72.9, SV72.10, SV73.10
unnamed: SV72.7, SV72.8, SV73.8
unnamed: SV72.5, SV72.6, SV73.6
unnamed: SV72.3, SV72.4, SV73.4
unnamed: SV72.1, SV72.2, SV73.2
unnamed: SV74.35, SV74.36, SV75.36
unnamed: SV74.33, SV74.34, SV75.34
unnamed: SV74.31, SV74.32, SV75.32
unnamed: SV74.29, SV74.30, SV75.30
unnamed: SV74.27, SV74.28, SV75.28
unnamed: SV74.25, SV74.26, SV75.26
unnamed: SV74.23, SV74.24, SV75.24
unnamed: SV74.21, SV74.22, SV75.22
unnamed: SV74.19, SV74.20, SV75.20
unnamed: SV74.17, SV74.18, SV75.18
unnamed: SV74.15, SV74.16, SV75.16
unnamed: SV74.13, SV74.14, SV75.14
unnamed: SV74.11, SV74.12, SV75.12
unnamed: SV74.9, SV74.10, SV75.10
unnamed: SV74.7, SV74.8, SV75.8
unnamed: SV74.5, SV74.6, SV75.6
unnamed: SV74.3, SV74.4, SV75.4
unnamed: SV74.1, SV74.2, SV75.2
unnamed: SV78.1, SV78.2, SV79.1
unnamed: SV78.3, SV78.4, SV79.3
unnamed: SV78.5, SV78.6, SV79.5
unnamed: SV78.7, SV78.8, SV79.7
unnamed: SV78.9, SV78.10, SV79.9
unnamed: SV78.11, SV78.12, SV79.11
unnamed: SV78.13, SV78.14, SV79.13
unnamed: SV78.15, SV78.16, SV79.15
unnamed: SV78.17, SV78.18, SV79.17
unnamed: SV78.19, SV78.20, SV79.19
unnamed: SV78.21, SV78.22, SV79.21
unnamed: SV78.23, SV78.24, SV79.23
unnamed: SV78.25, SV78.26, SV79.25
unnamed: SV78.27, SV78.28, SV79.27
unnamed: SV78.29, SV78.30, SV79.29
unnamed: SV78.31, SV78.32, SV79.31
unnamed: SV78.33, SV78.34, SV79.33
unnamed: SV78.35, SV78.36, SV79.35
unnamed: SV78.37, SV78.38, SV79.37
unnamed: SV78.39, SV78.40, SV79.39
unnamed: SV76.1, SV76.2, SV77.1
unnamed: SV76.3, SV76.4, SV77.3
unnamed: SV76.5, SV76.6, SV77.5
unnamed: SV76.7, SV76.8, SV77.7
unnamed: SV76.9, SV76.10, SV77.9
unnamed: SV76.11, SV76.12, SV77.11
unnamed: SV76.13, SV76.14, SV77.13
unnamed: SV76.15, SV76.16, SV77.15
unnamed: SV76.17, SV76.18, SV77.17
unnamed: SV76.19, SV76.20, SV77.19
unnamed: SV76.21, SV76.22, SV77.21
unnamed: SV76.23, SV76.24, SV77.23
unnamed: SV76.25, SV76.26, SV77.25
unnamed: SV76.27, SV76.28, SV77.27
unnamed: SV76.29, SV76.30, SV77.29
unnamed: SV76.31, SV76.32, SV77.31
unnamed: SV76.33, SV76.34, SV77.33
unnamed: SV76.35, SV76.36, SV77.35
unnamed: SV80.39, SV80.40, SV81.40
unnamed: SV80.37, SV80.38, SV81.38
unnamed: SV80.35, SV80.36, SV81.36
unnamed: SV80.33, SV80.34, SV81.34
unnamed: SV80.31, SV80.32, SV81.32
unnamed: SV80.29, SV80.30, SV81.30
unnamed: SV80.27, SV80.28, SV81.28
unnamed: SV80.25, SV80.26, SV81.26
unnamed: SV80.23, SV80.24, SV81.24
unnamed: SV80.21, SV80.22, SV81.22
unnamed: SV80.19, SV80.20, SV81.20
unnamed: SV80.17, SV80.18, SV81.18
unnamed: SV80.15, SV80.16, SV81.16
unnamed: SV80.13, SV80.14, SV81.14
unnamed: SV80.11, SV80.12, SV81.12
unnamed: SV80.9, SV80.10, SV81.10
unnamed: SV80.7, SV80.8, SV81.8
unnamed: SV80.5, SV80.6, SV81.6
unnamed: SV80.3, SV80.4, SV81.4
unnamed: SV80.1, SV80.2, SV81.2
unnamed: SV82.35, SV82.36, SV83.36
unnamed: SV82.33, SV82.34, SV83.34
unnamed: SV82.31, SV82.32, SV83.32
unnamed: SV82.29, SV82.30, SV83.30
unnamed: SV82.27, SV82.28, SV83.28
unnamed: SV82.25, SV82.26, SV83.26
unnamed: SV82.23, SV82.24, SV83.24
unnamed: SV82.21, SV82.22, SV83.22
unnamed: SV82.19, SV82.20, SV83.20
unnamed: SV82.17, SV82.18, SV83.18
unnamed: SV82.15, SV82.16, SV83.16
unnamed: SV82.13, SV82.14, SV83.14
unnamed: SV82.11, SV82.12, SV83.12
unnamed: SV82.9, SV82.10, SV83.10
unnamed: SV82.7, SV82.8, SV83.8
unnamed: SV82.5, SV82.6, SV83.6
unnamed: SV82.3, SV82.4, SV83.4
unnamed: SV82.1, SV82.2, SV83.2
unnamed: SV86.1, SV86.2, SV87.1
unnamed: SV86.3, SV86.4, SV87.3
unnamed: SV86.5, SV86.6, SV87.5
unnamed: SV86.7, SV86.8, SV87.7
unnamed: SV86.9, SV86.10, SV87.9
unnamed: SV86.11, SV86.12, SV87.11
unnamed: SV86.13, SV86.14, SV87.13
unnamed: SV86.15, SV86.16, SV87.15
unnamed: SV86.17, SV86.18, SV87.17
unnamed: SV86.19, SV86.20, SV87.19
unnamed: SV86.21, SV86.22, SV87.21
unnamed: SV86.23, SV86.24, SV87.23
unnamed: SV86.25, SV86.26, SV87.25
unnamed: SV86.27, SV86.28, SV87.27
unnamed: SV86.29, SV86.30, SV87.29
unnamed: SV86.31, SV86.32, SV87.31
unnamed: SV86.33, SV86.34, SV87.33
unnamed: SV86.35, SV86.36, SV87.35
unnamed: SV86.37, SV86.38, SV87.37
unnamed: SV86.39, SV86.40, SV87.39
unnamed: SV84.1, SV84.2, SV85.1
unnamed: SV84.3, SV84.4, SV85.3
unnamed: SV84.5, SV84.6, SV85.5
unnamed: SV84.7, SV84.8, SV85.7
unnamed: SV84.9, SV84.10, SV85.9
unnamed: SV84.11, SV84.12, SV85.11
unnamed: SV84.13, SV84.14, SV85.13
unnamed: SV84.15, SV84.16, SV85.15
unnamed: SV84.17, SV84.18, SV85.17
unnamed: SV84.19, SV84.20, SV85.19
unnamed: SV84.21, SV84.22, SV85.21
unnamed: SV84.23, SV84.24, SV85.23
unnamed: SV84.25, SV84.26, SV85.25
unnamed: SV84.27, SV84.28, SV85.27
unnamed: SV84.29, SV84.30, SV85.29
unnamed: SV84.31, SV84.32, SV85.31
unnamed: SV84.33, SV84.34, SV85.33
unnamed: SV84.35, SV84.36, SV85.35
unnamed: SV88.39, SV88.40, SV89.40
unnamed: SV88.37, SV88.38, SV89.38
unnamed: SV88.35, SV88.36, SV89.36
unnamed: SV88.33, SV88.34, SV89.34
unnamed: SV88.31, SV88.32, SV89.32
unnamed: SV88.29, SV88.30, SV89.30
unnamed: SV88.27, SV88.28, SV89.28
unnamed: SV88.25, SV88.26, SV89.26
unnamed: SV88.23, SV88.24, SV89.24
unnamed: SV88.21, SV88.22, SV89.22
unnamed: SV88.19, SV88.20, SV89.20
unnamed: SV88.17, SV88.18, SV89.18
unnamed: SV88.15, SV88.16, SV89.16
unnamed: SV88.13, SV88.14, SV89.14
unnamed: SV88.11, SV88.12, SV89.12
unnamed: SV88.9, SV88.10, SV89.10
unnamed: SV88.7, SV88.8, SV89.8
unnamed: SV88.5, SV88.6, SV89.6
unnamed: SV88.3, SV88.4, SV89.4
unnamed: SV88.1, SV88.2, SV89.2
unnamed: SV90.35, SV90.36, SV91.36
unnamed: SV90.33, SV90.34, SV91.34
unnamed: SV90.31, SV90.32, SV91.32
unnamed: SV90.29, SV90.30, SV91.30
unnamed: SV90.27, SV90.28, SV91.28
unnamed: SV90.25, SV90.26, SV91.26
unnamed: SV90.23, SV90.24, SV91.24
unnamed: SV90.21, SV90.22, SV91.22
unnamed: SV90.19, SV90.20, SV91.20
unnamed: SV90.17, SV90.18, SV91.18
unnamed: SV90.15, SV90.16, SV91.16
unnamed: SV90.13, SV90.14, SV91.14
unnamed: SV90.11, SV90.12, SV91.12
unnamed: SV90.9, SV90.10, SV91.10
unnamed: SV90.7, SV90.8, SV91.8
unnamed: SV90.5, SV90.6, SV91.6
unnamed: SV90.3, SV90.4, SV91.4
unnamed: SV90.1, SV90.2, SV91.2
unnamed: B1.K2, U$6.K2
unnamed: B1.J2, U$6.J2
unnamed: B1.H2, U$6.H2
unnamed: B1.L2, U$6.L2
unnamed: B1.M2, U$6.M2
unnamed: B1.N2, U$6.N2
unnamed: B1.P2, U$6.P2
unnamed: B1.F2, U$6.F2
unnamed: B1.E2, U$6.E2
unnamed: B1.D2, U$6.D2
unnamed: B1.R2, U$6.R2
unnamed: B1.S2, U$6.S2
unnamed: B1.B2, U$6.B2
unnamed: B1.T2, U$6.T2
unnamed: B1.U2, U$6.U2
unnamed: B1.V2, U$6.V2
unnamed: B1.A1, U$6.A1
unnamed: B1.V1, U$6.V1
unnamed: B1.U1, U$6.U1
unnamed: B1.T1, U$6.T1
unnamed: B1.S1, U$6.S1
unnamed: B1.R1, U$6.R1
unnamed: B1.P1, U$6.P1
unnamed: B1.N1, U$6.N1
unnamed: B1.M1, U$6.M1
unnamed: B1.L1, U$6.L1
unnamed: B1.K1, U$6.K1
unnamed: B1.J1, U$6.J1
unnamed: B1.H1, U$6.H1
unnamed: B1.F1, U$6.F1
unnamed: B1.E1, U$6.E1
unnamed: B1.D1, U$6.D1
unnamed: B1.C1, U$6.C1
unnamed: B1.B1, U$6.B1
unnamed: SV94.1, SV94.2, SV95.1
unnamed: SV94.3, SV94.4, SV95.3
unnamed: SV94.5, SV94.6, SV95.5
unnamed: SV94.7, SV94.8, SV95.7
unnamed: SV94.9, SV94.10, SV95.9
unnamed: SV94.11, SV94.12, SV95.11
unnamed: SV94.13, SV94.14, SV95.13
unnamed: SV94.15, SV94.16, SV95.15
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
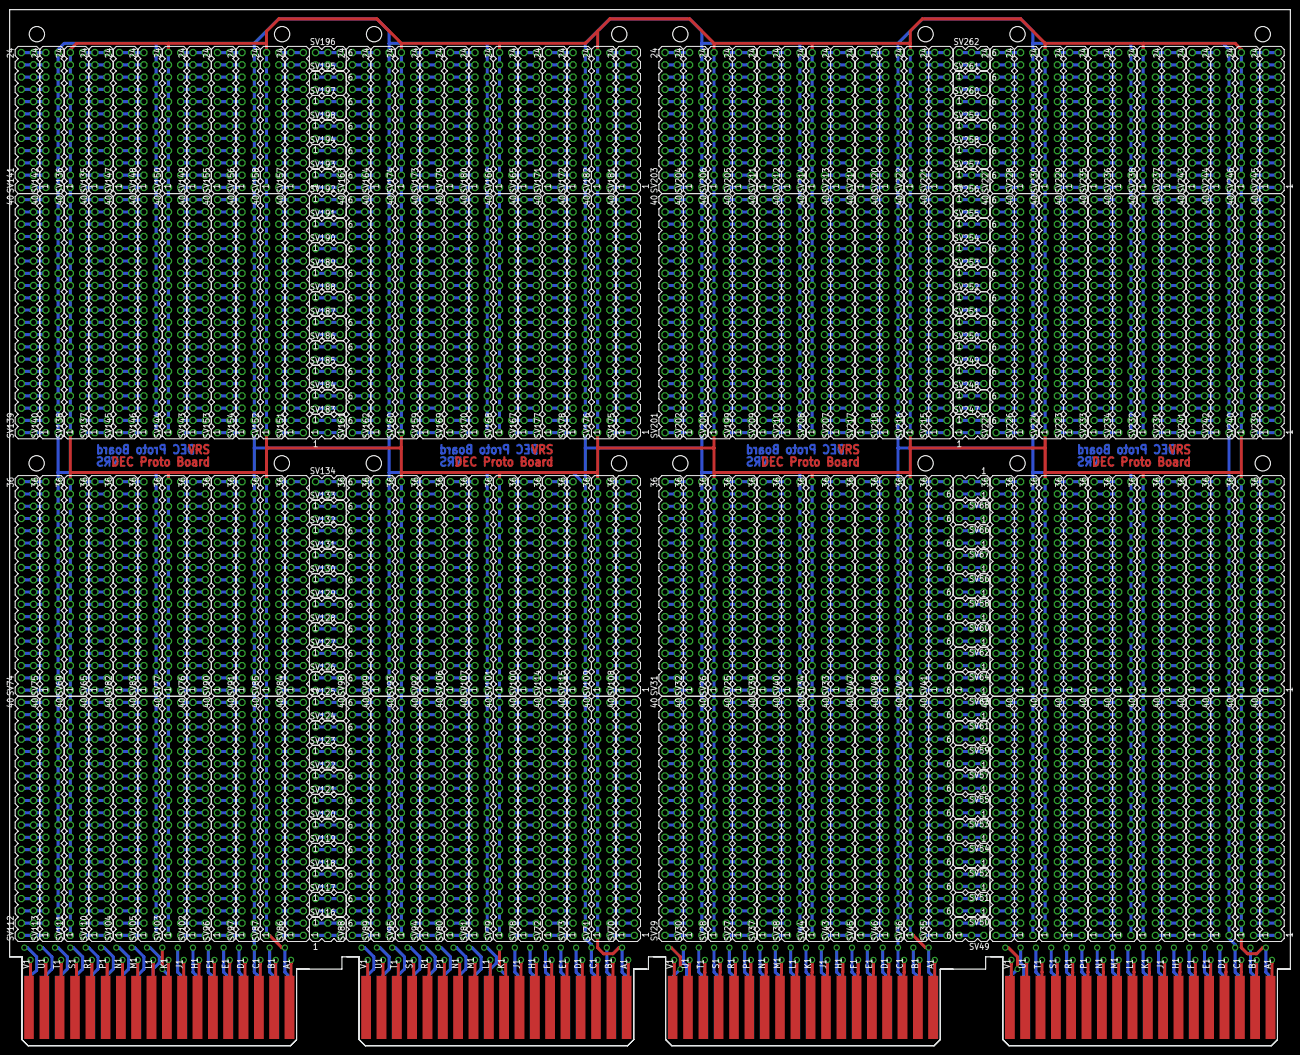
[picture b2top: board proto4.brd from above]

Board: 2 copper layers, 265.3 x 214.6 mm, 271 parts (0 on the bottom side), 1958 nets.
